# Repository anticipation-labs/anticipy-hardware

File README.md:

# Anticipy Hardware

Consolidated hardware record for the Anticipy pendant — a wearable that listens passively,
pulls tasks out of conversation, and acts on them without commands.

**Assembled:** 2026-09-06 · **Files:** 3756 (1189 unique) · **Size:** ~656M B
**Sources consolidated:** 15 separate packages plus loose files and sealed original zips from
Downloads, Desktop and Documents.

---

## The one thing to read first

> **Nothing here is fabrication-ready. There is no released Gerber, ODB++, drill file,
> pick-and-place, assembly drawing or final enclosure drawing anywhere in this repository.**
>
> There is, however, a **live JLCPCB order** (`W2026083114248171` / `SMT026083160845`) with an
> **unresolved part substitution** awaiting DFM review. See [07_PROCUREMENT](07_PROCUREMENT/).
> That is the only clock currently running.

> ⚠️ **Do not flash `anticipy.uf2` from any `~/AnticipyFleet/*/firmware/` lane.** That file is the
> image formally classified `UNVERIFIED_DO_NOT_FLASH` (sha256 `2e78015e…`, 624,640 bytes), sitting
> under a clean name next to a build receipt that describes a *different* 509,440-byte image.
> Details: [`00_START_HERE/CONTRADICTIONS.md`](00_START_HERE/CONTRADICTIONS.md) §14.

**New to this project?** Read [`00_START_HERE/ORIENTATION.md`](00_START_HERE/ORIENTATION.md) first.
It assumes no prior context: what the product is, where it actually stands, how to open every file
type here, what the vocabulary means, and what to do in your first week.

Then read [`00_START_HERE/HARDWARE_STATE.md`](00_START_HERE/HARDWARE_STATE.md) — one page on what
is actually true today — followed by
[`00_START_HERE/CONTRADICTIONS.md`](00_START_HERE/CONTRADICTIONS.md), which lists **seventeen** places
where two documents in this repository disagree with each other. Read that **before** acting on any
single document, because several of them contradict each other on the processor, the enclosure
size and the state of the board.

---

## Folder map

| Folder | What it is | Fab status |
|---|---|---|
| [`00_START_HERE/`](00_START_HERE/) | Orientation for newcomers, state, contradictions, glossary, provenance | — |
| [`01_CURRENT_TARGET_R1/`](01_CURRENT_TARGET_R1/) | The live requirement set (2026-09-04). What the incoming engineer is asked to build. | Not designed yet |
| [`02_PROTOTYPE_XIAO/`](02_PROTOTYPE_XIAO/) | XIAO nRF52840 Sense proof unit — wiring, enclosure CAD, assembly evidence | Proof only, on physical-test hold |
| [`03_PCB/`](03_PCB/) | Every custom board design. Three exist. None are releasable. | **NOT FOR FAB** |
| [`04_MECHANICAL/`](04_MECHANICAL/) | Enclosure CAD — print-ready, reference STEP, superseded meshes | Print-ready ≠ production |
| [`05_FIRMWARE/`](05_FIRMWARE/) | Source, build/protocol/threat docs, distinct images, device recovery | Lab only |
| [`06_FACTORY_AND_QA/`](06_FACTORY_AND_QA/) | Factory release process, QA fixtures, test evidence | Process defined, not executed |
| [`07_PROCUREMENT/`](07_PROCUREMENT/) | BOMs, order sheets, sourcing, **live JLCPCB order status** | Active |
| [`08_HISTORICAL_PACKAGES/`](08_HISTORICAL_PACKAGES/) | All 12 source packages plus the original zips, preserved verbatim. Never edit. | Archive |
| [`99_MANIFESTS/`](99_MANIFESTS/) | `SHA256SUMS.txt`, `INVENTORY.csv` | — |

**Folders `01`–`07` are a curated working view. Folder `08` is the provenance record.**
Every file in `01`–`07` also exists in `08`, byte-identical. If the two ever disagree, `08` wins.

---

## The five board generations, decoded

This is the single most confusing thing in the project, so it is stated once, plainly:

| Name | What it actually is | Where | State |
|---|---|---|---|
| **R0** | `ANT-PROD-R0 EVT`. First custom board. Has 31 commits of routing history. | `03_PCB/R0_ROUTING_HISTORY_NOT_FOR_FAB/` | 23 non-GND nets still unconnected |
| **R0B** | Revision B of R0. The "engineering checkpoint" the master package leads with. | `03_PCB/R0B_CHECKPOINT_NOT_FOR_FAB/` | 176 connections unrouted |
| **EVT-A** | `anticipy_evt_a`. A *separate* board from the 2026-08-28 Execution package, targeting a **different processor**. | `03_PCB/EVT_A_2026-08-28_SUPERSEDED/` | Fabrication hold: 0 segments, 0 vias, 0 zones |
| **ESP32-S3** | The prior generation (April 2026). Different SoC, mic, charger and enclosure entirely. Holds the only packaging spec and manufacturing-order doc that exist. | `08_HISTORICAL_PACKAGES/2026-04_esp32s3_prior_generation/` | Superseded |
| **R1** | The current target. **Does not exist yet** — brief only. | `01_CURRENT_TARGET_R1/` | Not started |

R0 and R0B are not the same file, and the copy of R0 shipped inside the master package is **not**
the same file as the one in the R0 git repository. See `00_START_HERE/CONTRADICTIONS.md`.

---

## Working with this repository

### Cloning

```bash
git lfs install                                    # once per machine
git clone https://github.com/anticipation-labs/anticipy-hardware.git
```

Git LFS is required, but only barely — it is scoped to exactly **two** files, the oversized
superseded meshes under `04_MECHANICAL/SUPERSEDED_AND_MOCKUPS/OVERSIZED_MESHES_500mah_2026-08-22/`
(68.8 MB and 64.8 MB). Everything else is stored as ordinary git objects deliberately, so a clone
never depends on an LFS bandwidth quota. If LFS is unavailable, `GIT_LFS_SKIP_SMUDGE=1 git clone`
still gets you the entire repository minus those two superseded files.

### Byte fidelity

`.gitattributes` sets `* -text`, disabling all end-of-line conversion. This is not cosmetic: this
repository is a checksum-verified archive, and EOL rewriting would silently invalidate
`99_MANIFESTS/SHA256SUMS.txt` for every CSV that arrived with CRLF endings.

### The R0 routing history

The R0 KiCad project arrived as its own git repository with 31 commits and no remote. A nested
`.git` cannot be committed into a parent repository, so the history is preserved as a bundle:

```bash
cd 03_PCB/R0_ROUTING_HISTORY_NOT_FOR_FAB
git clone R0_ROUTING_HISTORY.bundle r0-history      # full 31-commit history, restored
```

`R0_ROUTING_HISTORY_COMMITS.txt` lists every commit, and
`R0_UNCOMMITTED_AT_ARCHIVE_TIME.txt` records the working-tree changes that were uncommitted when
this archive was made. Those uncommitted files are present in the folder as-is.

### What is deliberately not ignored

`.kicad_prl` and other KiCad per-user state arrived inside the original handoff packages and are
covered by the checksum manifest, so they are committed rather than ignored. Only `__pycache__`
bytecode and macOS `.DS_Store` files were removed.

---

## Verifying this folder

```bash
cd ~/Anticipy-Hardware && shasum -a 256 -c 99_MANIFESTS/SHA256SUMS.txt
```

`99_MANIFESTS/INVENTORY.csv` lists every file with its hash, size, date and owning folder.

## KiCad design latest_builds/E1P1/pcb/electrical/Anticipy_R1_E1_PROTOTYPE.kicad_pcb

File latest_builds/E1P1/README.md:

# Anticipy E1P1 — Boston build handoff, 9 September 2026

Use this package for the current custom E1P1 prototype. It contains the released PCB, matching oval case geometry, exact component checklist, programming image and researched rush-manufacturing plan. It supersedes the older oval review package for this build. Files are prepared; no supplier slot or Saturday delivery is booked.

## Open these first

- **See the product:** `cad/Oval_E1_Port_and_Controls.png` and `cad/Oval_E1_Exploded_Labeled.png`.
- **Open the PCB and schematic:** `pcb/electrical/Anticipy_R1_E1_PROTOTYPE.kicad_pro` in KiCad 10.0.6. The board and schematic are beside it. Keep the local libraries with the project.
- **Read the circuit and fabrication drawings:** `E1P1_Fabrication_and_Assembly.pdf`.
- **See the assembled case:** `cad/Oval_E1_Assembly_FIT_CANDIDATE.step`.
- **Buy only missing parts:** `procurement/Missing_Parts.csv`; its companion notes distinguish purchase/delivery records from physically counted stock. Do not buy the full BOM again without checking owned quantities.
- **Manufacturing and delivery:** `logistics/Manufacturing_Saturday_Plan.md`.

## Dimensions and matching files

The PCB is **45.75 × 17.88 × 0.8 mm**. The oval shell is **56 × 35 × 14.8 mm nominal**. The case contains the selected protected Jauch LP561836JU+PCM+2 WIRES 50MM battery, motor and routed wire allowances. **This design does not meet the requested 30 × 14 × 8 mm product size.**

The native PCB SHA-256 is `78fe28acde6ceb3ab33aac8af503d4c418540cce31979cc91d3add5e5d0bec36`. The case was regenerated against this exact PCB, including the moved USB protection part and selected component body limits. See the CAD contract and verification receipts. No copper was altered while packaging this handoff.

## What to give each shop

**PCB fabrication/assembly shop:** `pcb/manufacturing/` in full, the PDF, `pcb/electrical/` for native review, and the exact missing/consigned-part list. This is four-layer 0.8 mm FR-4/ENIG, with **all 137 vias epoxy-filled, planarized and copper-capped (IPC-4761 Type VII)**, controlled-impedance USB and 47 fitted SMT references per board. The four USB mounting slots remain open. Do not order a generic tented-via tier. Ask for 20 passing assemblies plus appropriate scrap/feeder allowance; two first articles should pass before completing the balance. The quantity file includes two additional-board spares, but this is not a guaranteed yield allowance.

**Case printer:** `cad/Front_Oval_Shell.step`, `Rear_Service_Cover.step`, `Button_Plunger.step` and their STLs. `Oval_E1_Three_Print_Parts_GEOMETRY_ONLY.3mf` holds those three opaque pieces in millimetres; it is not sliced G-code. `Clear_Lightpipe.step` / `.stl` is a fourth, separate optical piece requiring clear material. Read `cad/Mechanical_Handoff.md` for supports, fit, screw pilots, insulation, adhesive and acoustic details. Print unfilled nonconductive polymer; gold in the pictures is display color. Do not print the whole assembled or exploded STEP as one solid.

**Final integrator:** both shop packages, `programming/`, the external wiring/BOM files in `pcb/manufacturing/`, the CAD harness contract and the procurement checklist. Use the specified battery/motor/sensor polarities and inspect/test the open assembly before closure.

## What is verified, and what is still unfinished

The released copper has **0 native DRC violations, 0 unconnected items, 0 schematic parity issues and 0 ERC violations**. Independent saved-copper checks connect all 45 named nets. The CAD has passing geometric checks against the stated component/harness allowances. These are computer checks, not physical tests.

The supplied firmware is for supervised first-power and live-audio bring-up. **Charging is disabled. Complete offline NAND recording/recovery/backfill, qualified charging, signed updates and device ownership remain unfinished.** No assembled E1 unit has demonstrated 16-hour runtime, 24-hour recording retention, charging temperature, radio range, acoustic quality or drop performance. This package is not a qualified customer-wearable release; purchasing parts and assembling boards will not by itself finish that firmware work.

The target is 20 engineering prototypes, at least 15 working, in Boston by Saturday 12 September. The plan needs a manufacturer to accept the complete rush job, usable radio modules at that assembler, physical first-article success, and a booked recipient handoff. BU's normal mailroom can add 24–72 hours after a carrier delivery scan. The logistics file gives current phone numbers and the fastest routes found, without claiming an unaccepted quote or delivery promise.

`PCB_Release_Readme.md` and `RELEASE_STATUS.json` preserve the PCB release scope. `SHA256SUMS` and `HANDOFF_MANIFEST.json` identify the final contents of this combined handoff.

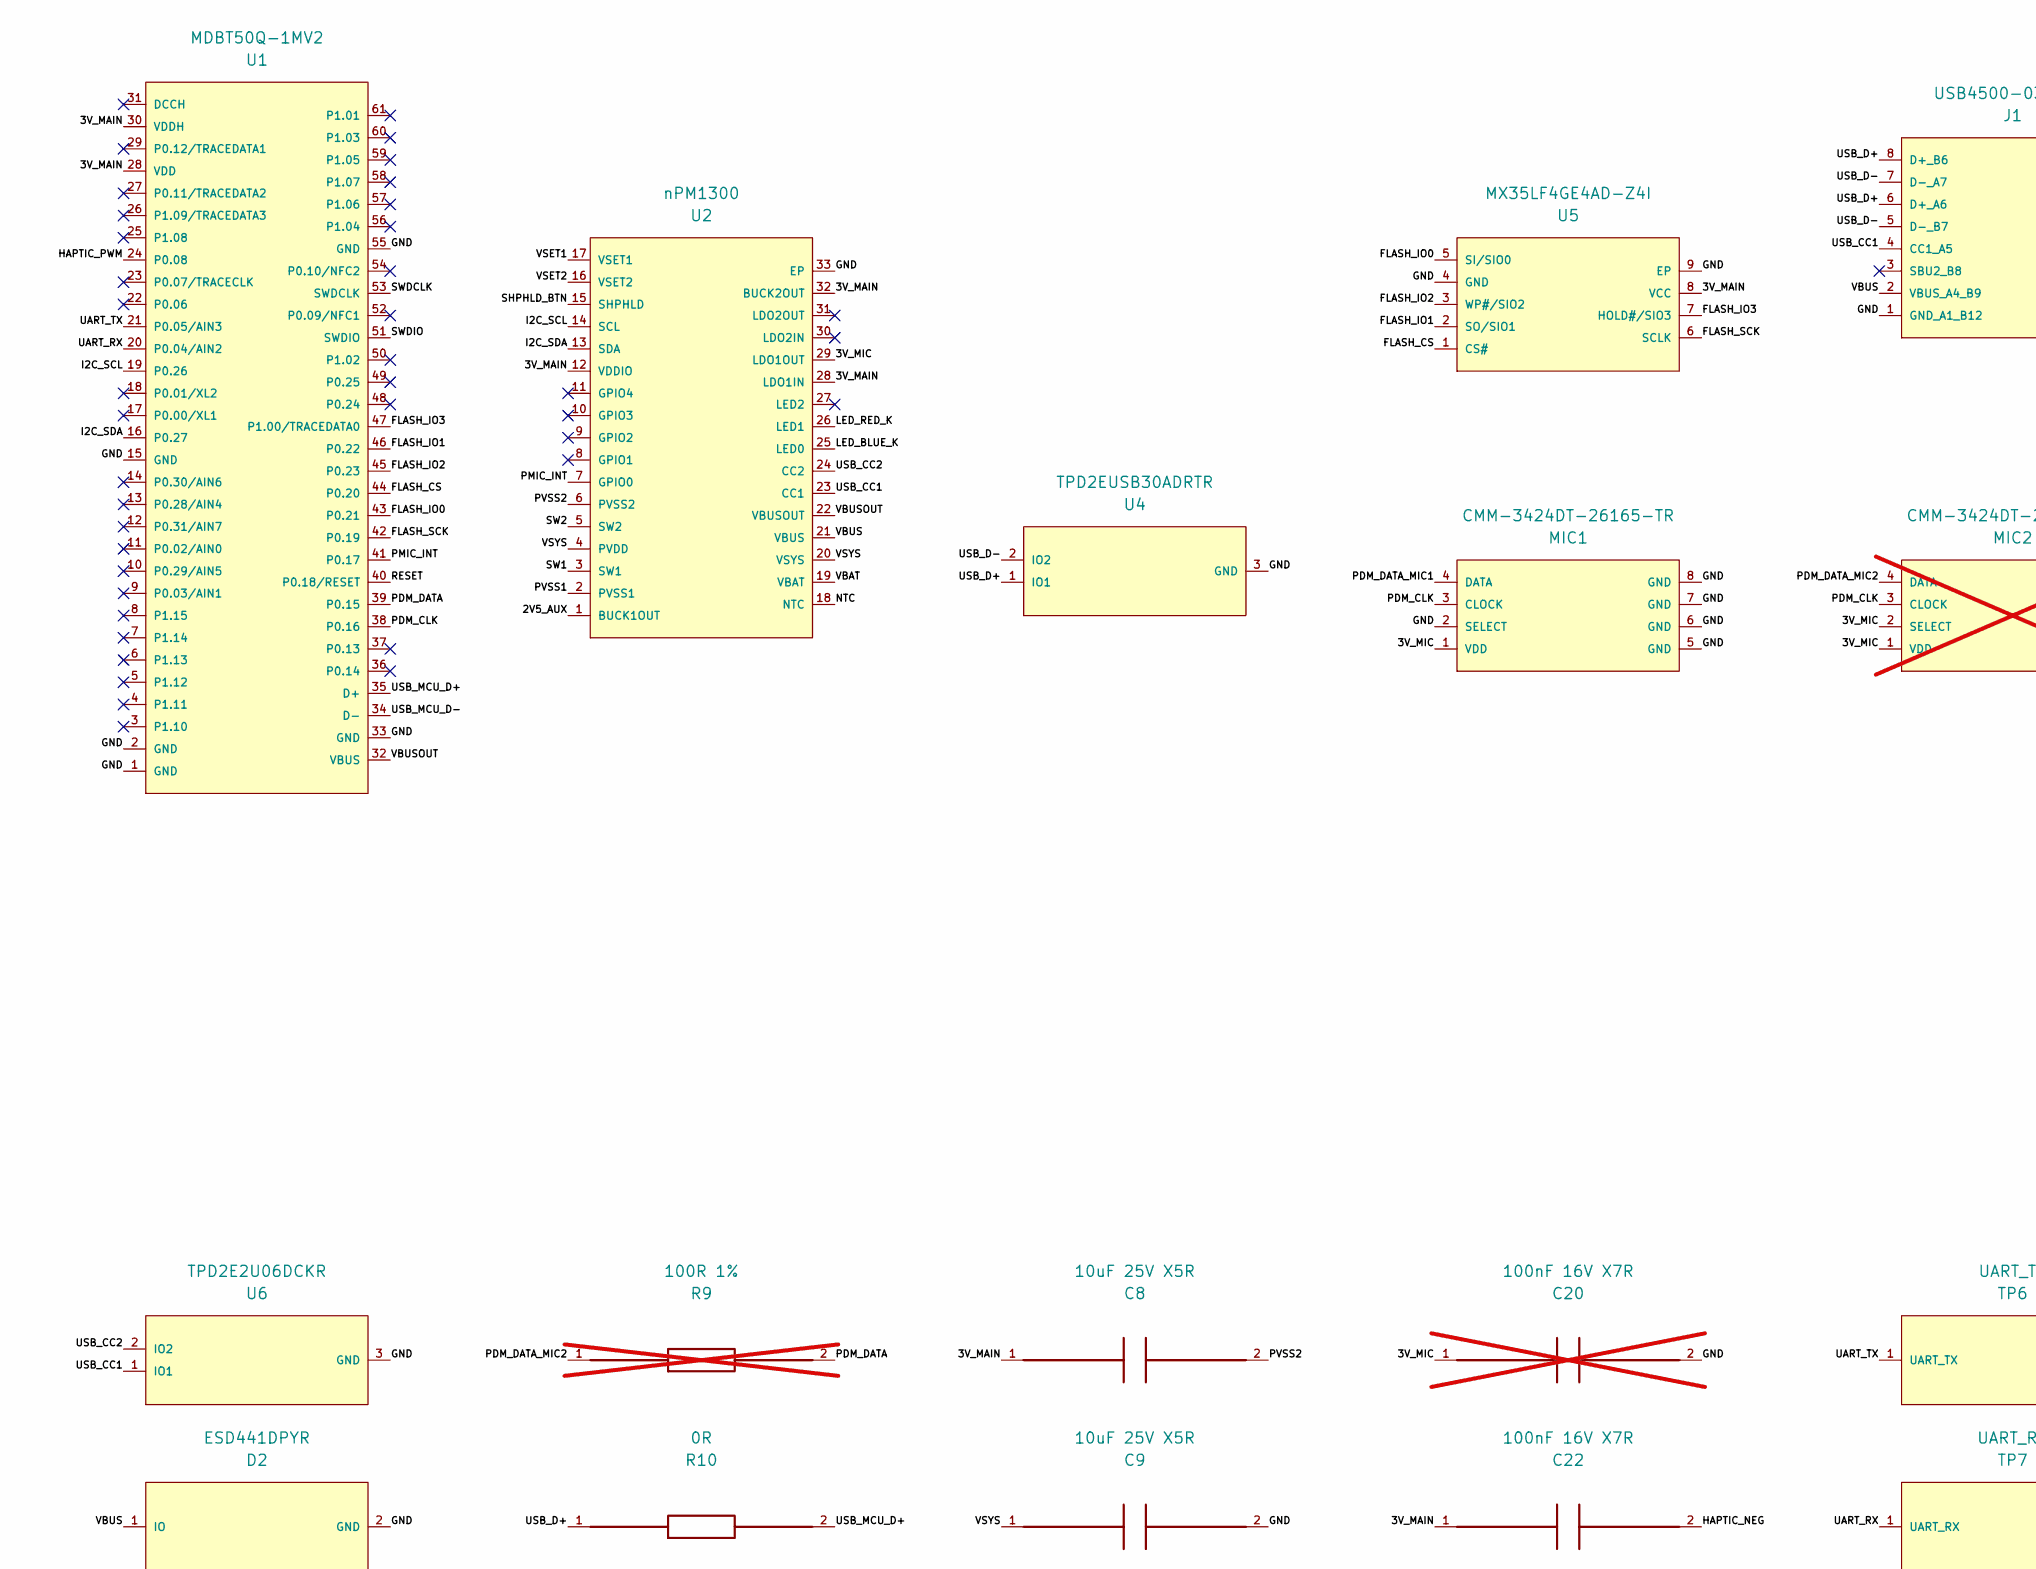
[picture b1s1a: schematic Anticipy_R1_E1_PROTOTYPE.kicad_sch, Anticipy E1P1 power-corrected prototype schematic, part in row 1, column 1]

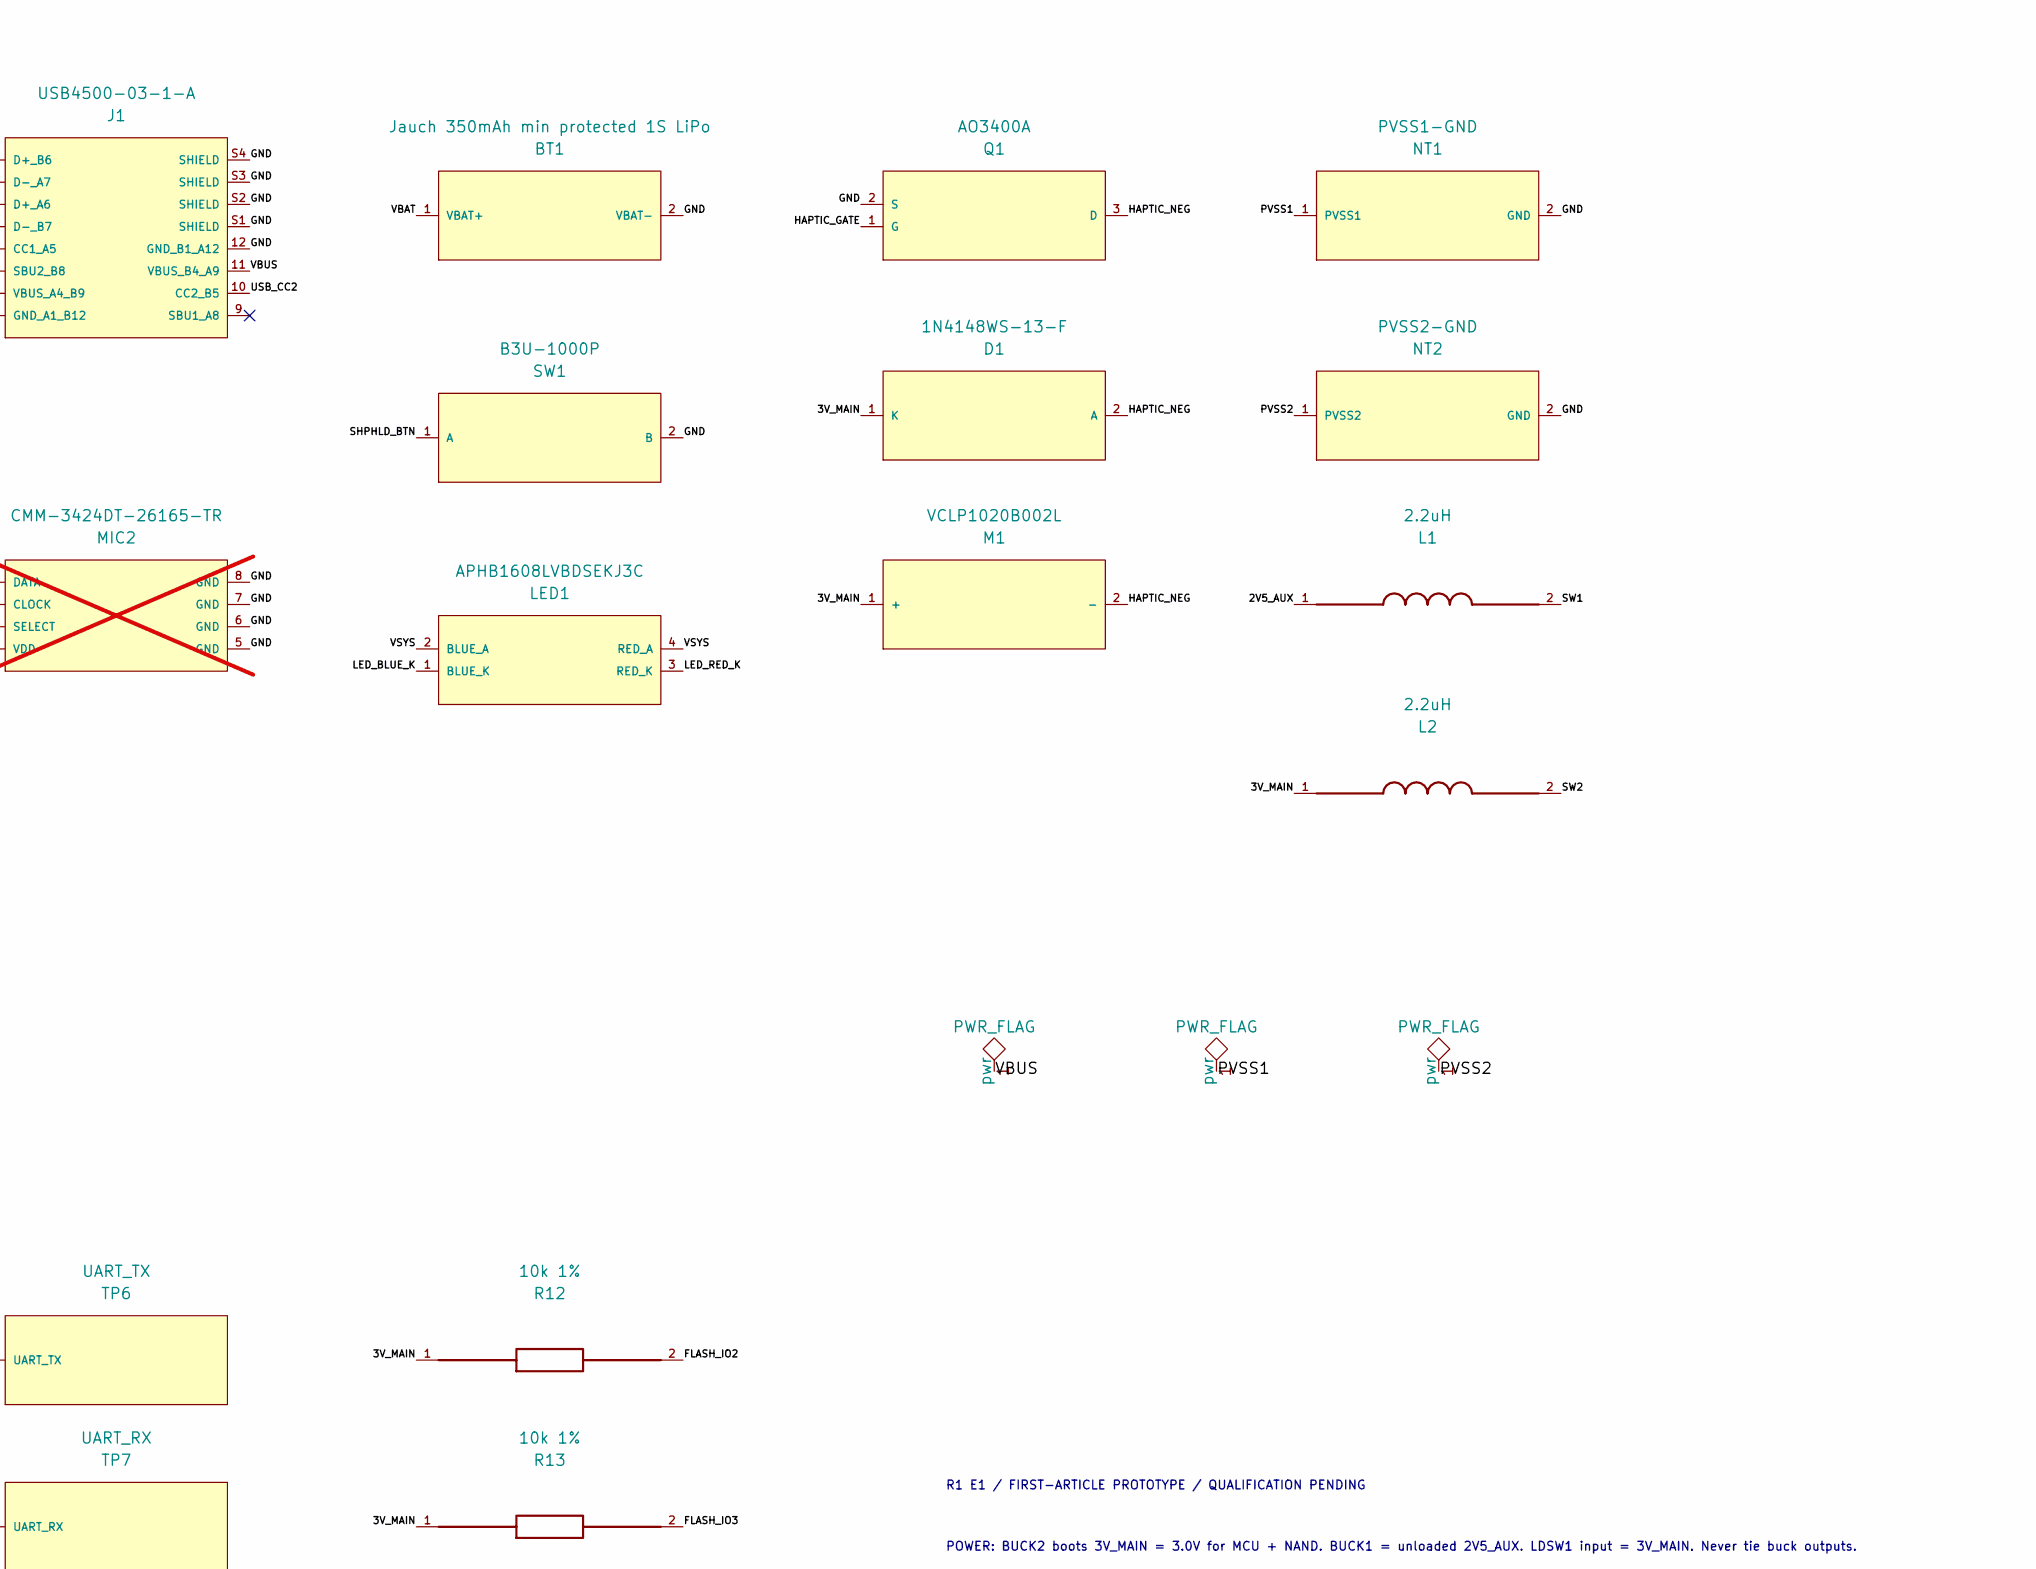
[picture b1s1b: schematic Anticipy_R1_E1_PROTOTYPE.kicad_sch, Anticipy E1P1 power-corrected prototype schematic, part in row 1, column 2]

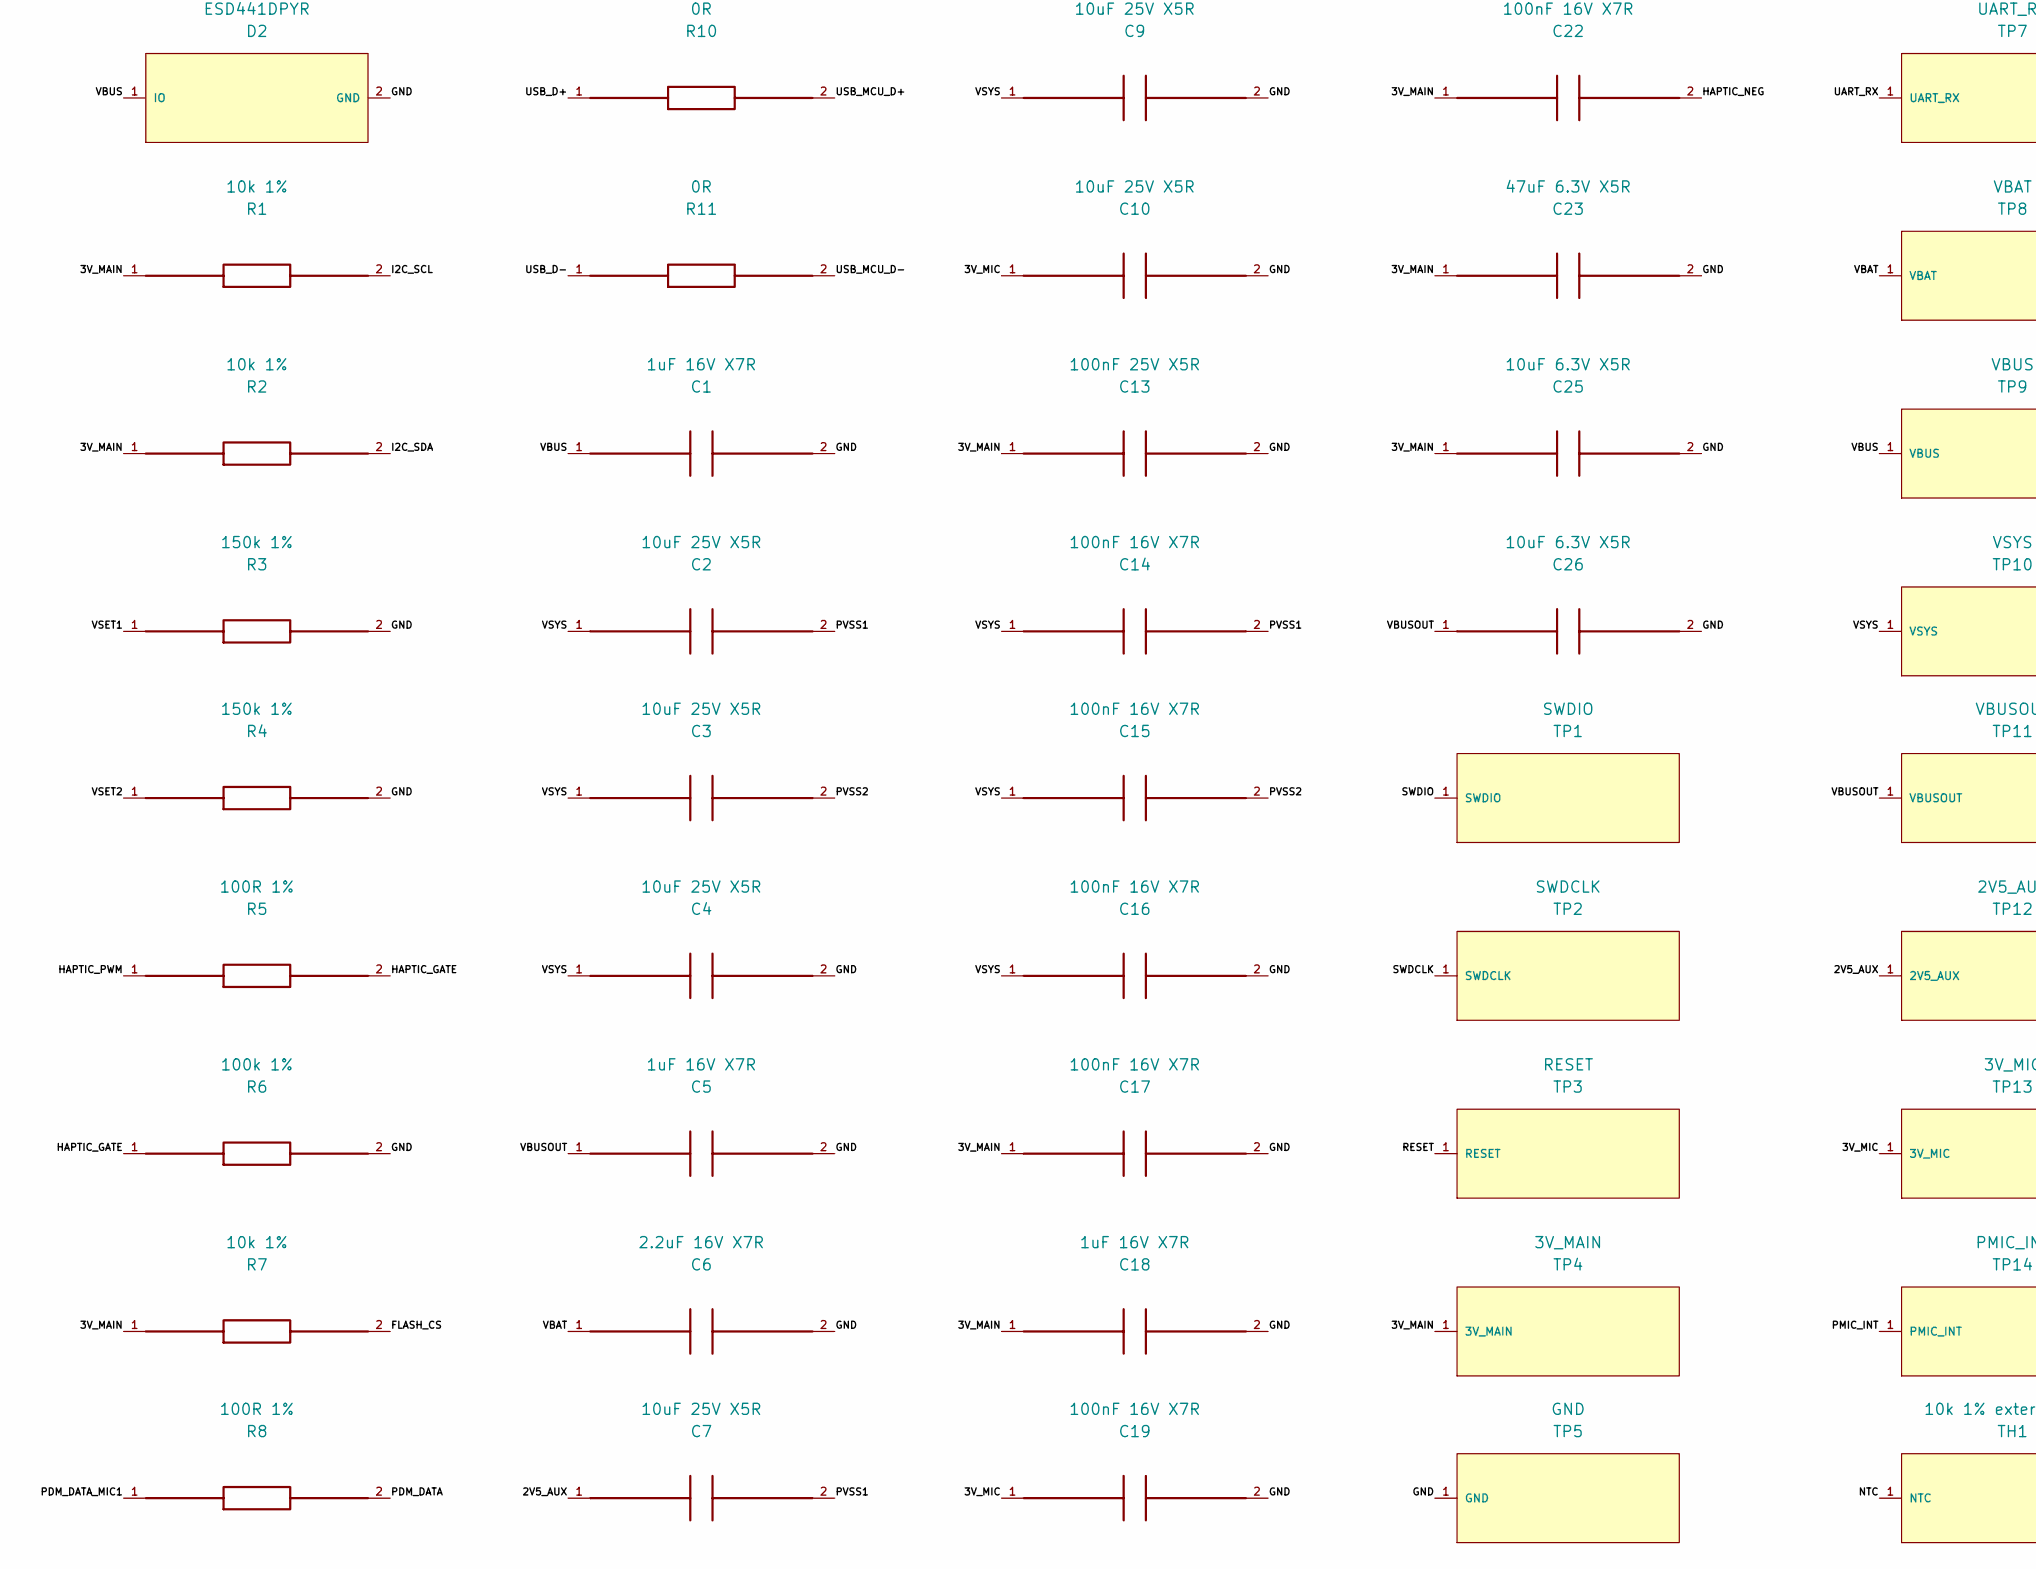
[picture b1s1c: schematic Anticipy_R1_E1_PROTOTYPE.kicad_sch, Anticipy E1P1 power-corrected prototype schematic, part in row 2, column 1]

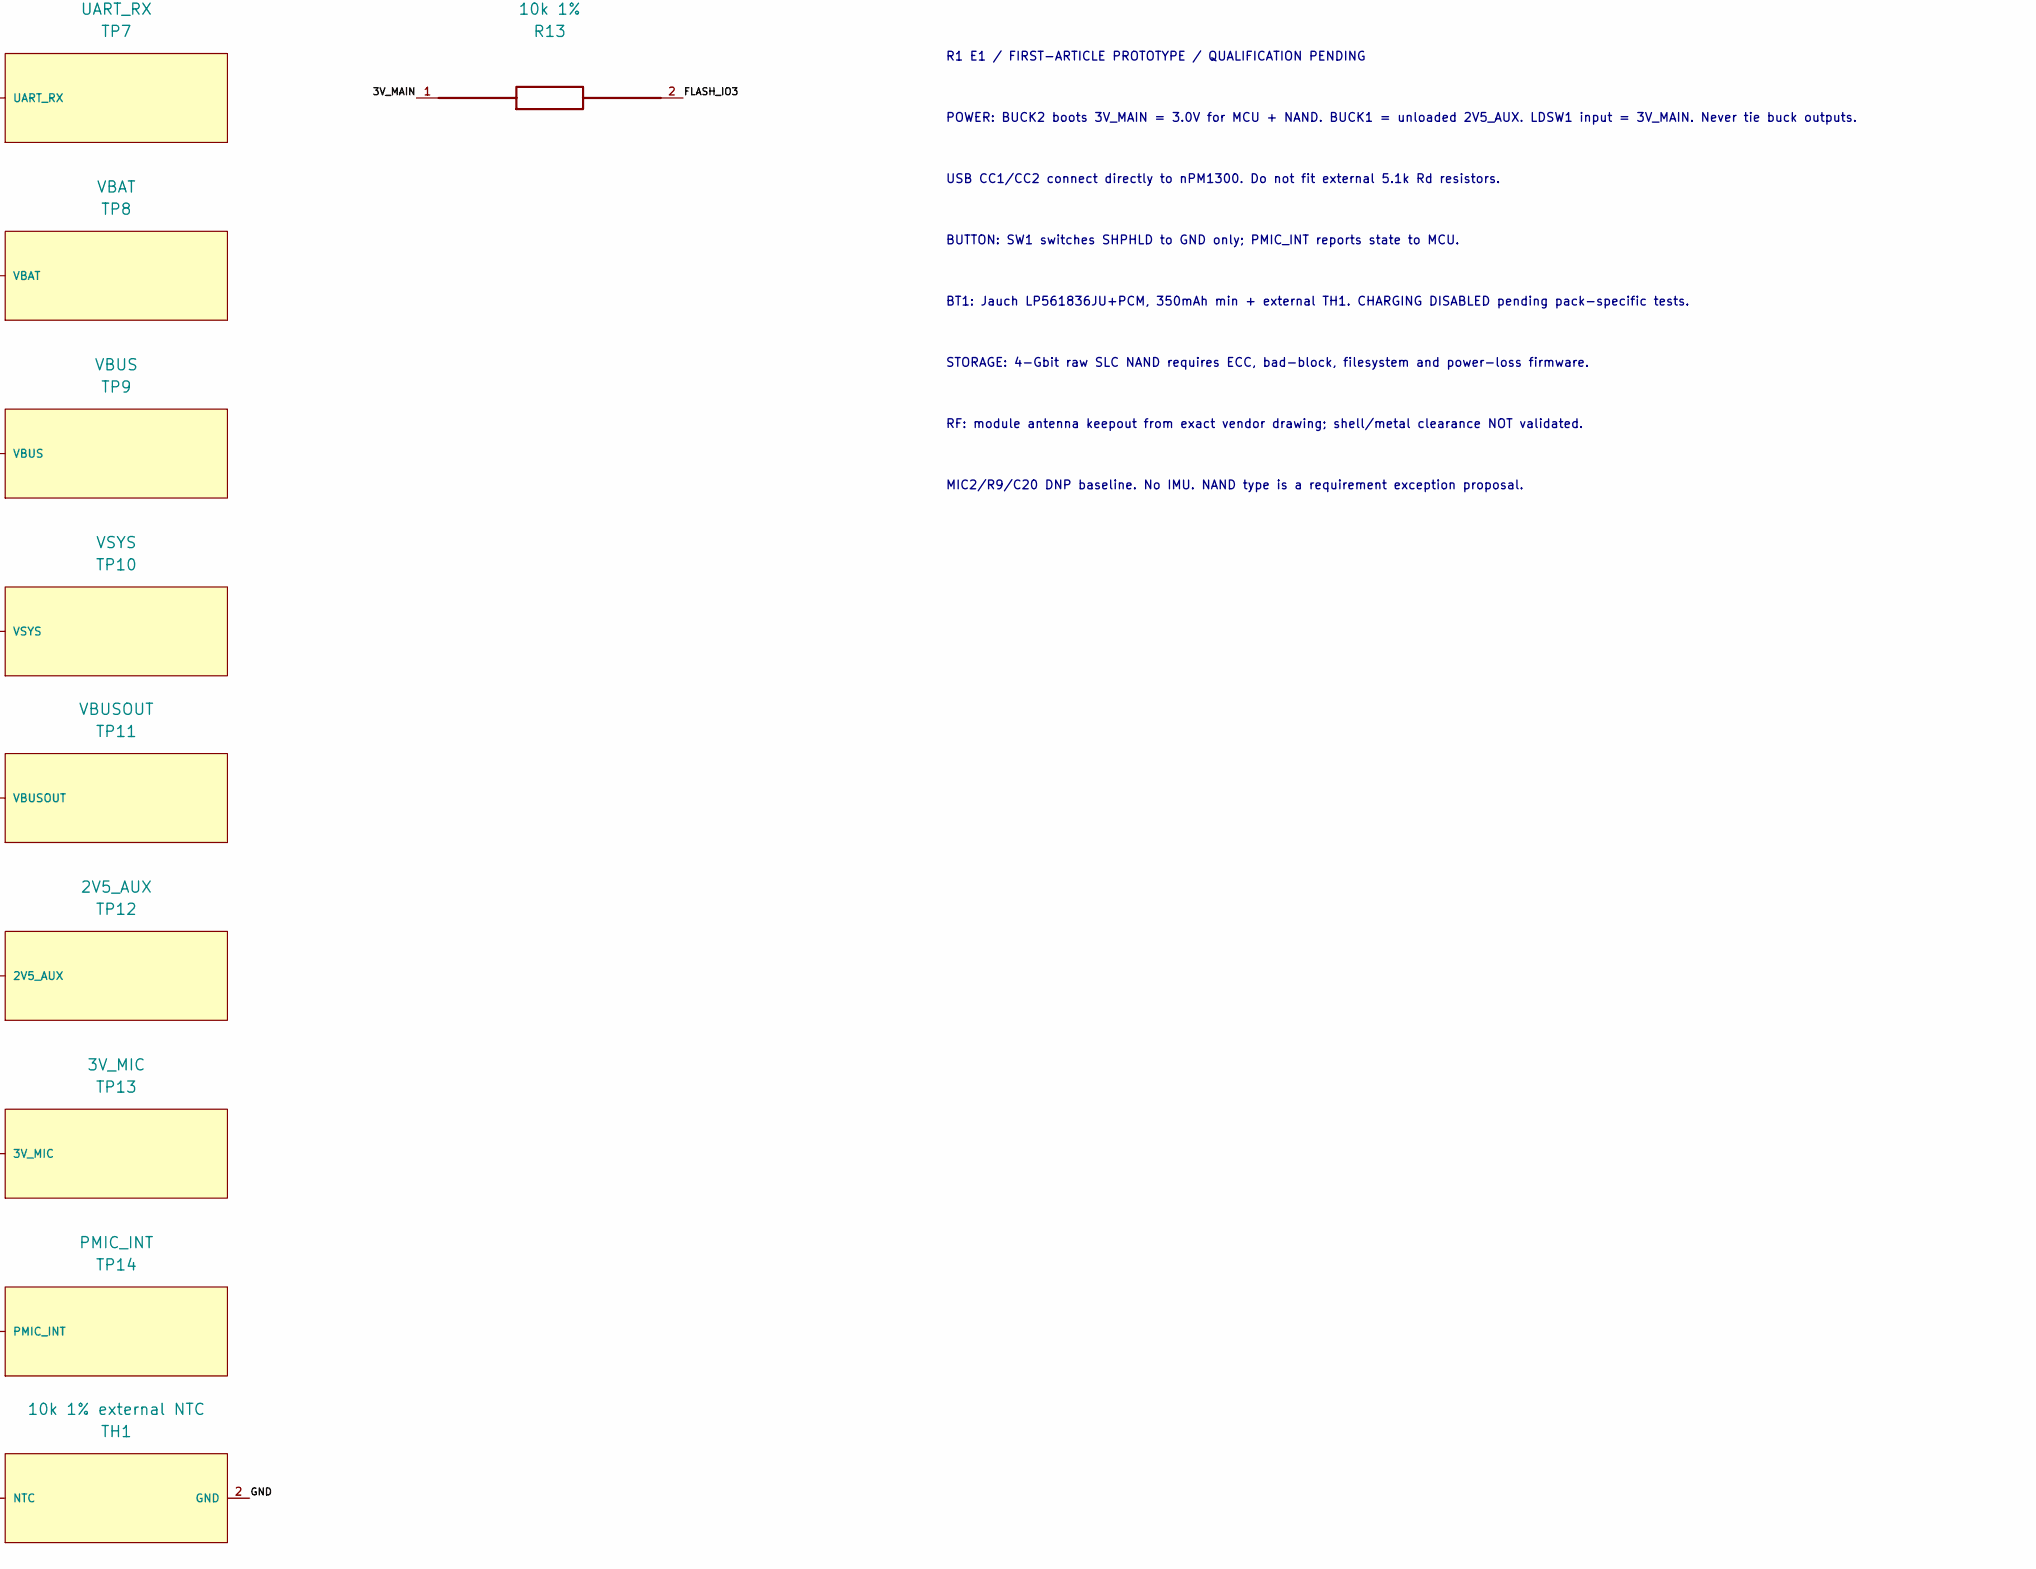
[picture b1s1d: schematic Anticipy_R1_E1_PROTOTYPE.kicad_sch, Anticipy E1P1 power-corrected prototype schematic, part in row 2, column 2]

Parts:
BT1: Jauch 350mAh min protected 1S LiPo; BT1__WirePads_2_P1.27mm; MPN LP561836JU+PCM+2 WIRES 50MM
C1: 1uF 16V X7R; C1__C_0603_1608Metric; MPN C1608X7R1C105K080AC
C2: 10uF 25V X5R; C2__C_0603_1608Metric; MPN GRM188R61E106MA73D
C3: 10uF 25V X5R; C3__C_0603_1608Metric; MPN GRM188R61E106MA73D
C4: 10uF 25V X5R; C4__C_0603_1608Metric; MPN GRM188R61E106MA73D
C5: 1uF 16V X7R; C5__C_0603_1608Metric; MPN C1608X7R1C105K080AC
C6: 2.2uF 16V X7R; C6__C_0603_1608Metric; MPN EMK107BB7225KA-T
C7: 10uF 25V X5R; C7__C_0603_1608Metric; MPN GRM188R61E106MA73D
C8: 10uF 25V X5R; C8__C_0603_1608Metric; MPN GRM188R61E106MA73D
C9: 10uF 25V X5R; C9__C_0603_1608Metric; MPN GRM188R61E106MA73D
C10: 10uF 25V X5R; C10__C_0603_1608Metric; MPN GRM188R61E106MA73D
C13: 100nF 25V X5R; C13__C_0201_0603Metric; MPN C0603X5R1E104K030BB
C14: 100nF 16V X7R; C14__C_0402_1005Metric; MPN C0402C104M4RACTU
C15: 100nF 16V X7R; C15__C_0402_1005Metric; MPN C0402C104M4RACTU
C16: 100nF 16V X7R; C16__C_0402_1005Metric; MPN C0402C104M4RACTU
C17: 100nF 16V X7R; C17__C_0402_1005Metric; MPN C1005X7R1C104K050BC
C18: 1uF 16V X7R; C18__C_0603_1608Metric; MPN C1608X7R1C105K080AC
C19: 100nF 16V X7R; C19__C_0402_1005Metric; MPN C1005X7R1C104K050BC
C20: 100nF 16V X7R; C20__C_0402_1005Metric; MPN C1005X7R1C104K050BC; not fitted
C22: 100nF 16V X7R; C22__C_0402_1005Metric; MPN C1005X7R1C104K050BC
C23: 47uF 6.3V X5R; C23__C_0805_2012Metric; MPN GRM21BR60J476ME01L
C25: 10uF 6.3V X5R; C25__C_0402_1005Metric; MPN GRM155R60J106ME15D
C26: 10uF 6.3V X5R; C26__C_0402_1005Metric; MPN GRM155R60J106ME15D
D1: 1N4148WS-13-F; D1__D_SOD-323; MPN 1N4148WS-13-F
D2: ESD441DPYR; D2__TI_DPY0002A_X1SON; MPN ESD441DPYR
J1: USB4500-03-1-A; J1__USB_C_Receptacle_GCT_USB4500-03-1-A_MidMount; MPN USB4500-03-1-A
L1: 2.2uH; L1__L_Murata_DFE201610P; MPN CIGT201610EH2R2MNE
L2: 2.2uH; L2__L_Murata_DFE201610P; MPN CIGT201610EH2R2MNE
LED1: APHB1608LVBDSEKJ3C; LED1__LED_Kingbright_APHB1608LVBDSEKJ3C; MPN APHB1608LVBDSEKJ3C
M1: VCLP1020B002L; M1__WirePads_2_P1.27mm; MPN VCLP1020B002L
MIC1: CMM-3424DT-26165-TR; MIC1__SameSky_CMM-3424DT-26165-TR_TopPort_PDM; MPN CMM-3424DT-26165-TR
MIC2: CMM-3424DT-26165-TR; MIC2__SameSky_CMM-3424DT-26165-TR_TopPort_PDM; MPN CMM-3424DT-26165-TR; not fitted
NT1: PVSS1-GND; NT1__NetTie_Nordic_Config4; MPN NETTIE
NT2: PVSS2-GND; NT2__NetTie_Nordic_Config4; MPN NETTIE
Q1: AO3400A; Q1__SOT-23; MPN AO3400A
R1: 10k 1%; R1__R_0201_0603Metric; MPN RC0201FR-0710KL
R2: 10k 1%; R2__R_0201_0603Metric; MPN RC0201FR-0710KL
R3: 150k 1%; R3__R_0201_0603Metric; MPN RC0201FR-07150KL
R4: 150k 1%; R4__R_0201_0603Metric; MPN RC0201FR-07150KL
R5: 100R 1%; R5__R_0402_1005Metric; MPN RC0402FR-07100RL
R6: 100k 1%; R6__R_0402_1005Metric; MPN RC0402FR-07100KL
R7: 10k 1%; R7__R_0402_1005Metric; MPN RC0402FR-0710KL
R8: 100R 1%; R8__R_0402_1005Metric; MPN RC0402FR-07100RL
R9: 100R 1%; R9__R_0402_1005Metric; MPN RC0402FR-07100RL; not fitted
R10: 0R; R10__R_0201_0603Metric; MPN CRCW02010000Z0ED
R11: 0R; R11__R_0201_0603Metric; MPN CRCW02010000Z0ED
R12: 10k 1%; R12__R_0402_1005Metric; MPN RC0402FR-0710KL
R13: 10k 1%; R13__R_0402_1005Metric; MPN RC0402FR-0710KL
SW1: B3U-1000P; SW1__SW_SPST_B3U-1000P; MPN B3U-1000P
TH1: 10k 1% external NTC; TH1__WirePads_2_P1.27mm; MPN B57540G1103F000
TP1: SWDIO; TP1__PogoPad_D1.0mm; MPN TESTPAD
TP2: SWDCLK; TP2__PogoPad_D1.0mm; MPN TESTPAD
TP3: RESET; TP3__PogoPad_D1.0mm; MPN TESTPAD
TP4: 3V_MAIN; TP4__PogoPad_D1.0mm; MPN TESTPAD
TP5: GND; TP5__PogoPad_D1.0mm; MPN TESTPAD
TP6: UART_TX; TP6__PogoPad_D1.0mm; MPN TESTPAD
TP7: UART_RX; TP7__PogoPad_D1.0mm; MPN TESTPAD
TP8: VBAT; TP8__PogoPad_D1.0mm; MPN TESTPAD
TP9: VBUS; TP9__PogoPad_D1.0mm; MPN TESTPAD
TP10: VSYS; TP10__PogoPad_D1.0mm; MPN TESTPAD
TP11: VBUSOUT; TP11__PogoPad_D1.0mm; MPN TESTPAD
TP12: 2V5_AUX; TP12__PogoPad_D1.0mm; MPN TESTPAD
TP13: 3V_MIC; TP13__PogoPad_D1.0mm; MPN TESTPAD
TP14: PMIC_INT; TP14__PogoPad_D1.0mm; MPN TESTPAD
U1: MDBT50Q-1MV2; U1__Raytac_MDBT50Q_R0B; MPN MDBT50Q-1MV2
U2: nPM1300; U2__nPM1300_QFN32_Reference; MPN NPM1300-QEAA-R
U4: TPD2EUSB30ADRTR; U4__Texas_DRT-3_R0B; MPN TPD2EUSB30ADRTR
U5: MX35LF4GE4AD-Z4I; U5__WSON-8-1EP_8x6mm_P1.27mm_EP3.4x4.3mm; MPN MX35LF4GE4AD-Z4I
U6: TPD2E2U06DCKR; U6__TI_DCK_SC70_3_R0B; MPN TPD2E2U06DCKR

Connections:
/2V5_AUX: C7.1, L1.1, TP12.1 (2V5_AUX), U2.1 (BUCK1OUT)
/3V_MAIN: C8.1, C13.1, C17.1, C18.1, C22.1, C23.1, C25.1, D1.1 (K), L2.1, M1.1 (+), R1.1, R2.1, R7.1, R12.1, R13.1, TP4.1, U1.28 (VDD), U1.30 (VDDH), U2.12 (VDDIO), U2.28 (LDO1IN), U2.32 (BUCK2OUT), U5.8 (VCC)
/3V_MIC: C10.1, C19.1, C20.1, MIC1.1 (VDD), MIC2.1 (VDD), MIC2.2 (SELECT), TP13.1, U2.29 (LDO1OUT)
/FLASH_CS: R7.2, U1.44 (P0.20), U5.1 (CS#)
/FLASH_IO0: U1.43 (P0.21), U5.5 (SI/SIO0)
/FLASH_IO1: U1.46 (P0.22), U5.2 (SO/SIO1)
/FLASH_IO2: R12.2, U1.45 (P0.23), U5.3 (WP#/SIO2)
/FLASH_IO3: R13.2, U1.47 (P1.00/TRACEDATA0), U5.7 (HOLD#/SIO3)
/FLASH_SCK: U1.42 (P0.19), U5.6 (SCLK)
/GND: BT1.2 (VBAT-), C1.2, C4.2, C5.2, C6.2, C9.2, C10.2, C13.2, C16.2, C17.2, C18.2, C19.2, C20.2, C23.2, C25.2, C26.2, D2.2 (GND), J1.1 (GND_A1_B12), J1.12 (GND_B1_A12), J1.S1 (SHIELD), J1.S2 (SHIELD), J1.S3 (SHIELD), J1.S4 (SHIELD), MIC1.2 (SELECT), MIC1.5 (GND), MIC1.6 (GND), MIC1.7 (GND), MIC1.8 (GND), MIC2.5 (GND), MIC2.6 (GND), MIC2.7 (GND), MIC2.8 (GND), NT1.2 (GND), NT2.2 (GND), Q1.2 (S), R3.2, R4.2, R6.2, SW1.2 (B), TH1.2 (GND), TP5.1, U1.1 (GND), U1.2 (GND), U1.15 (GND), U1.33 (GND), U1.55 (GND), U2.33 (EP), U4.3 (GND), U5.4 (GND), U5.9 (EP), U6.3 (GND)
/HAPTIC_GATE: Q1.1 (G), R5.2, R6.1
/HAPTIC_NEG: C22.2, D1.2 (A), M1.2 (-), Q1.3 (D)
/HAPTIC_PWM: R5.1, U1.24 (P0.08)
/I2C_SCL: R1.2, U1.19 (P0.26), U2.14 (SCL)
/I2C_SDA: R2.2, U1.16 (P0.27), U2.13 (SDA)
/LED_BLUE_K: LED1.1 (BLUE_K), U2.25 (LED0)
/LED_RED_K: LED1.3 (RED_K), U2.26 (LED1)
/NTC: TH1.1 (NTC), U2.18 (NTC)
/PDM_CLK: MIC1.3 (CLOCK), MIC2.3 (CLOCK), U1.38 (P0.16)
/PDM_DATA: R8.2, R9.2, U1.39 (P0.15)
/PDM_DATA_MIC1: MIC1.4 (DATA), R8.1
/PDM_DATA_MIC2: MIC2.4 (DATA), R9.1
/PMIC_INT: TP14.1, U1.41 (P0.17), U2.7 (GPIO0)
/PVSS1: C2.2, C7.2, C14.2, NT1.1 (PVSS1), U2.2 (PVSS1)
/PVSS2: C3.2, C8.2, C15.2, NT2.1 (PVSS2), U2.6 (PVSS2)
/RESET: TP3.1, U1.40 (P0.18/RESET)
/SHPHLD_BTN: SW1.1 (A), U2.15 (SHPHLD)
/SW1: L1.2, U2.3 (SW1)
/SW2: L2.2, U2.5 (SW2)
/SWDCLK: TP2.1, U1.53 (SWDCLK)
/SWDIO: TP1.1, U1.51 (SWDIO)
/UART_RX: TP7.1, U1.20 (P0.04/AIN2)
/UART_TX: TP6.1, U1.21 (P0.05/AIN3)
/USB_CC1: J1.4 (CC1_A5), U2.23 (CC1), U6.1 (IO1)
/USB_CC2: J1.10 (CC2_B5), U2.24 (CC2), U6.2 (IO2)
/USB_D+: J1.6 (D+_A6), J1.8 (D+_B6), R10.1, U4.1 (IO1)
/USB_D-: J1.5 (D-_B7), J1.7 (D-_A7), R11.1, U4.2 (IO2)
/USB_MCU_D+: R10.2, U1.35 (D+)
/USB_MCU_D-: R11.2, U1.34 (D-)
/VBAT: BT1.1 (VBAT+), C6.1, TP8.1, U2.19 (VBAT)
/VBUS: C1.1, D2.1 (IO), J1.2 (VBUS_A4_B9), J1.11 (VBUS_B4_A9), TP9.1, U2.21 (VBUS)
/VBUSOUT: C5.1, C26.1, TP11.1, U1.32 (VBUS), U2.22 (VBUSOUT)
/VSET1: R3.1, U2.17 (VSET1)
/VSET2: R4.1, U2.16 (VSET2)
/VSYS: C2.1, C3.1, C4.1, C9.1, C14.1, C15.1, C16.1, LED1.2 (BLUE_A), LED1.4 (RED_A), TP10.1, U2.4 (PVDD), U2.20 (VSYS)

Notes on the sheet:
R1 E1 / FIRST-ARTICLE PROTOTYPE / QUALIFICATION PENDING
POWER: BUCK2 boots 3V_MAIN = 3.0V for MCU + NAND. BUCK1 = unloaded 2V5_AUX. LDSW1 input = 3V_MAIN. Never tie buck outputs.
USB CC1/CC2 connect directly to nPM1300. Do not fit external 5.1k Rd resistors.
BUTTON: SW1 switches SHPHLD to GND only; PMIC_INT reports state to MCU.
BT1: Jauch LP561836JU+PCM, 350mAh min + external TH1. CHARGING DISABLED pending pack-specific tests.
STORAGE: 4-Gbit raw SLC NAND requires ECC, bad-block, filesystem and power-loss firmware.
RF: module antenna keepout from exact vendor drawing; shell/metal clearance NOT validated.
MIC2/R9/C20 DNP baseline. No IMU. NAND type is a requirement exception proposal.

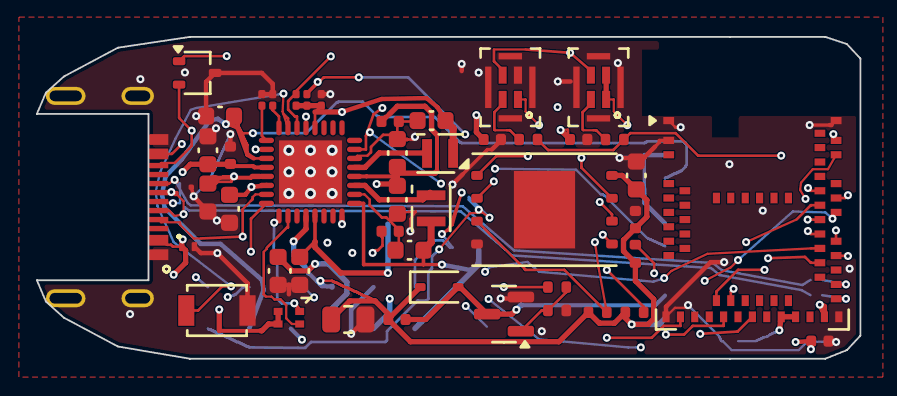
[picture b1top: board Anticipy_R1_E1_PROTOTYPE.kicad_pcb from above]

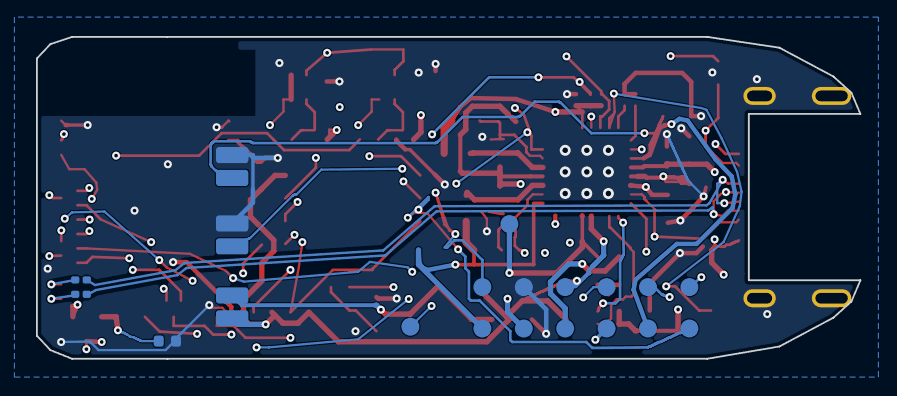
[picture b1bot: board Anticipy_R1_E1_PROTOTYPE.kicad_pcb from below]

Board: 4 copper layers, 45.8 x 17.9 mm, 69 parts (20 on the bottom side), 45 nets.
